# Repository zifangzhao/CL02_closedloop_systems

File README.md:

# CL02 Closed-Loop System

CL02 is a closed-loop electrophysiology trigger controller for detecting configured LFP oscillation features and driving timed stimulation outputs.

The project website is now built from the MkDocs source in [`docs/`](docs/) with configuration in [`mkdocs.yml`](mkdocs.yml). It documents:

- hardware connections and state indicators,
- Windows control-center setup and operation,
- trigger timing and external override behavior,
- firmware update workflow,
- firmware and MATLAB filter-design source locations.

## Local Documentation Preview

```powershell
pip install -r requirements.txt
mkdocs serve
```

For a strict build:

```powershell
mkdocs build --strict --verbose
```

## Repository Areas

| Area | Contents |
| --- | --- |
| `Windows` | CL02 control-center source, installers, and USB driver files. |
| `MCU` | STM32 firmware source, headers, filters, Keil project files, and firmware images. |
| `PCB` | CL02 board files, CAM outputs, assembly files, and BOM assets. |
| `Matlab` | Filter-design and validation scripts. |
| `docs` | MkDocs website source. |

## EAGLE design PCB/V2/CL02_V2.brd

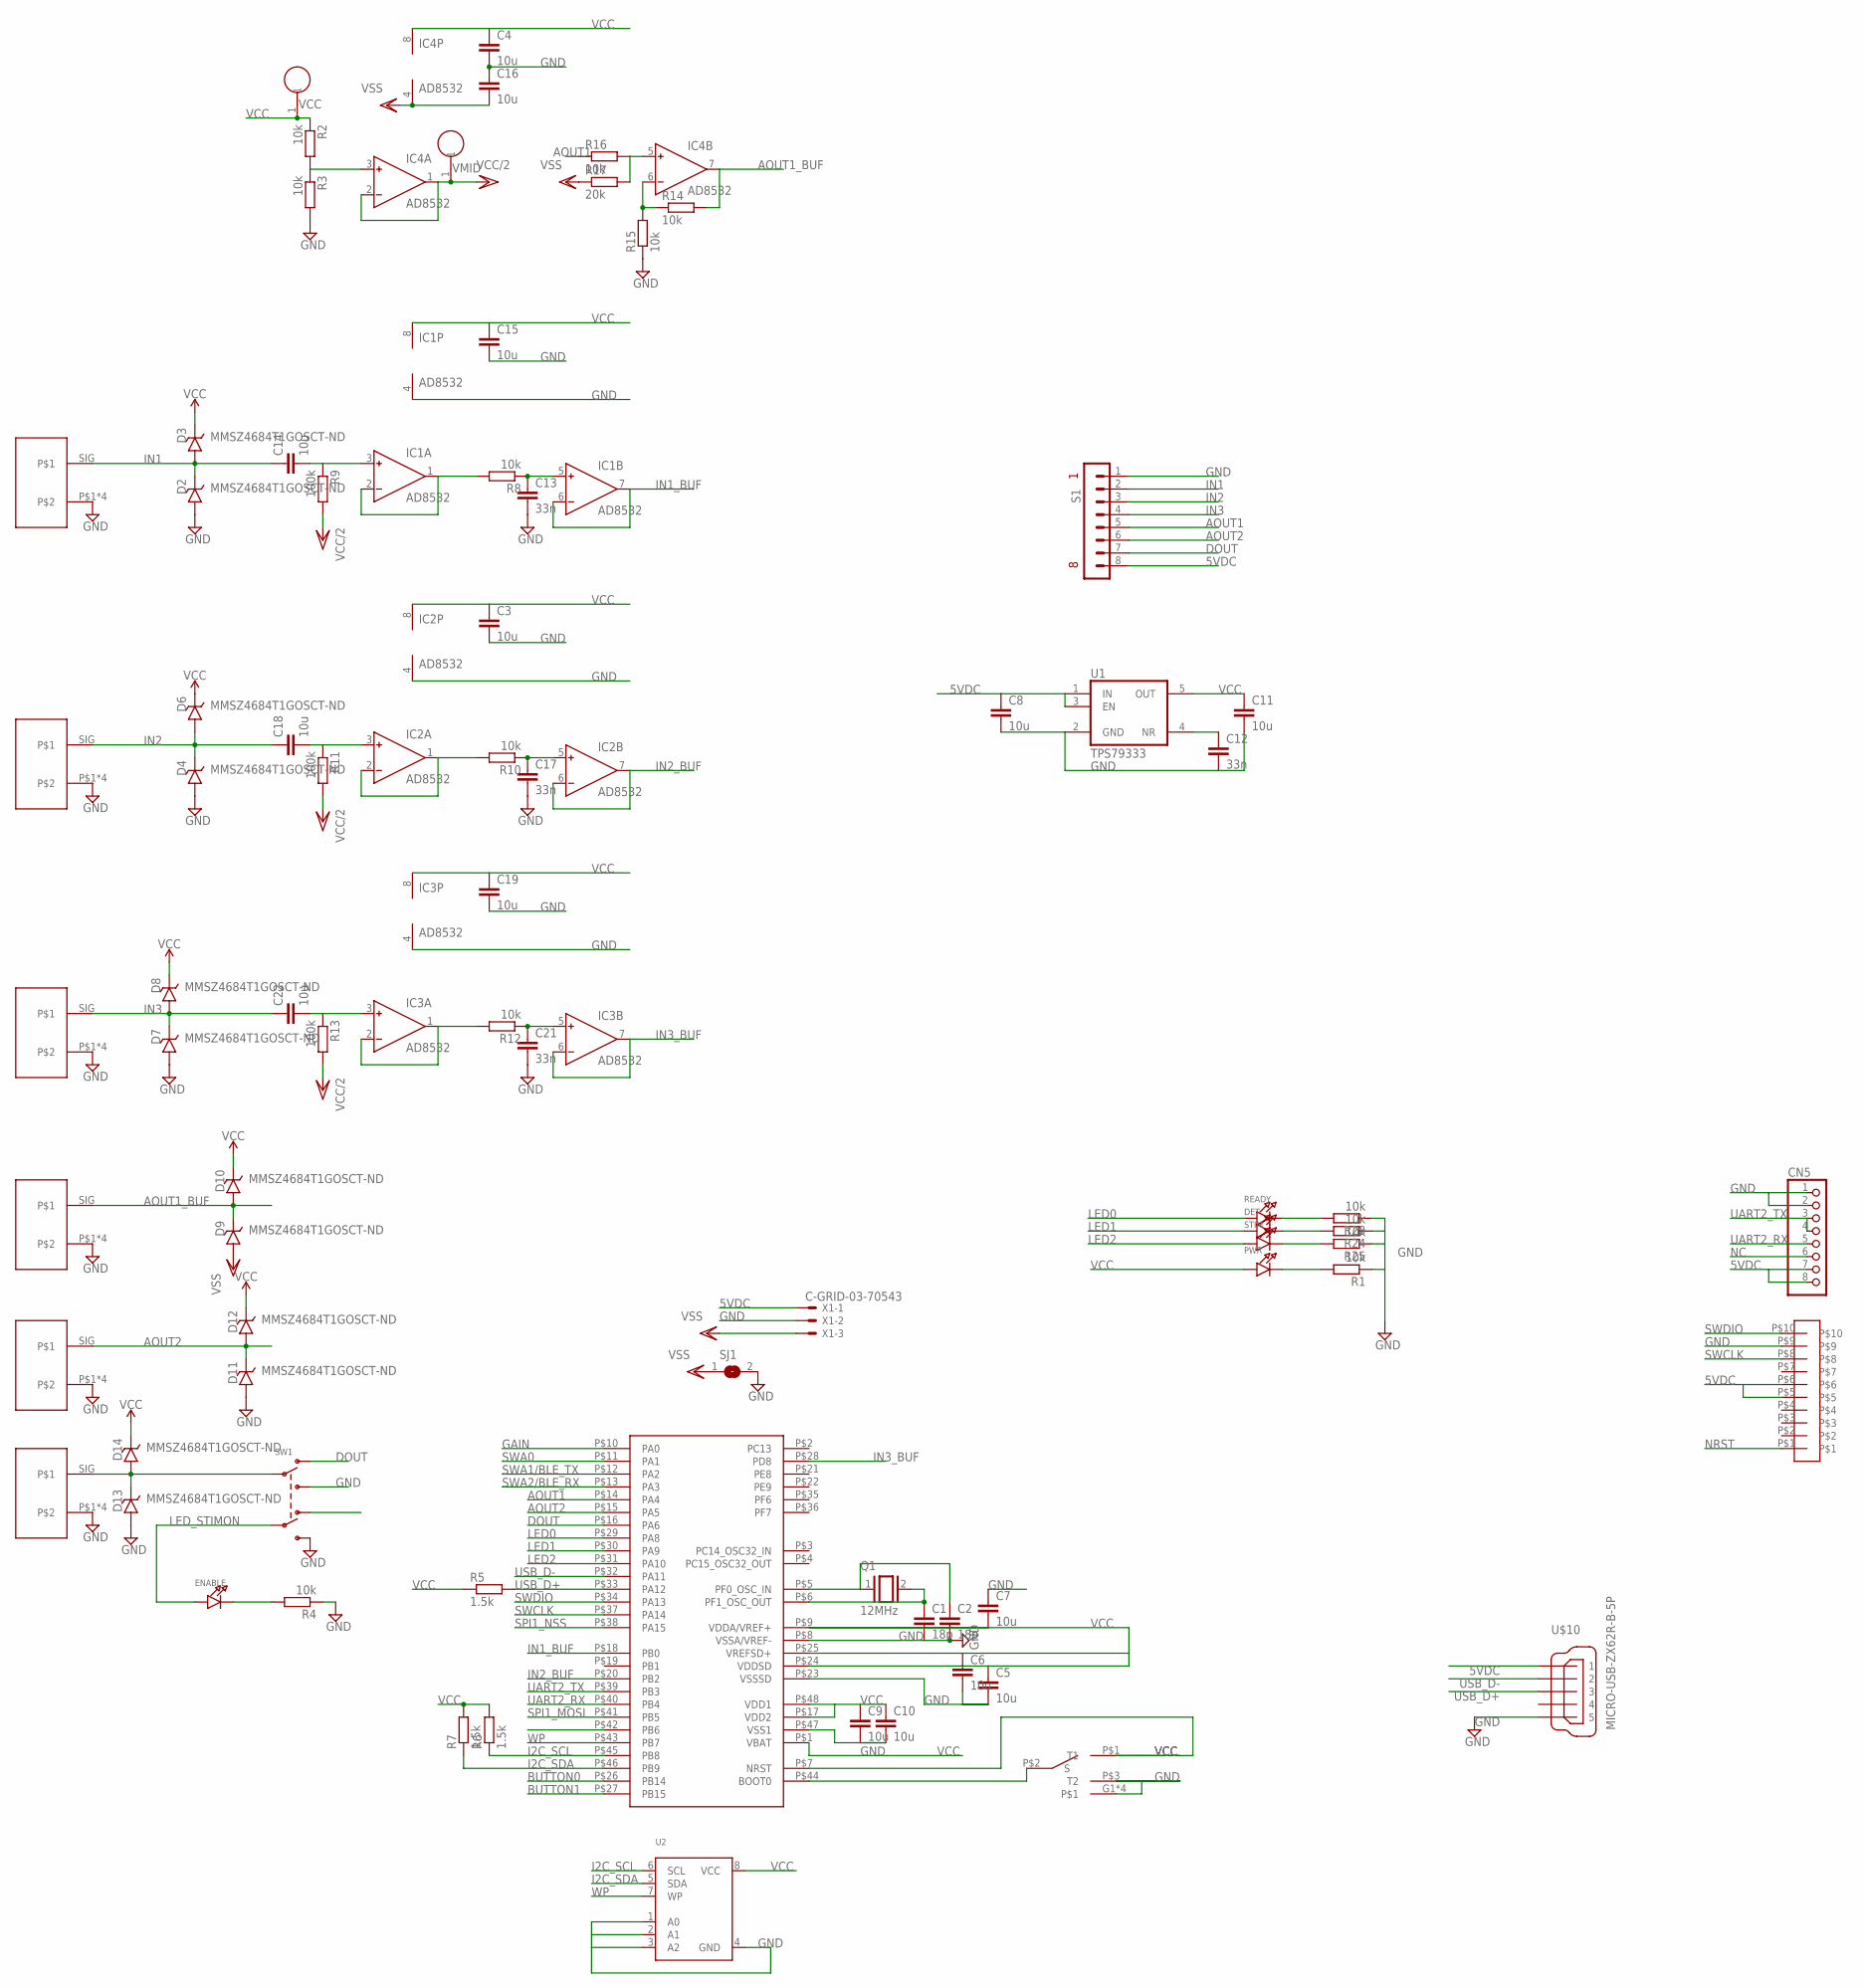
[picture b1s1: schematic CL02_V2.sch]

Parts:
A_OUT1, A_OUT2: BNC_8MM; BNC_V_8MM
C1, C2: 18p; C0402
C3, C4, C5, C6, C7, C8, C9, C10, C11, C14, C15, C16, C18, C19, C22: 10u; C0402
C12, C13, C17, C21: 33n; C0402
CN5: JST_8PIN; JSTPH8
D2, D3, D4, D6, D7, D8, D9, D10, D11, D12, D13, D14: MMSZ4684T1GOSCT-ND; SOD-123
DET: LED0603; CHIPLED_0603
D_OUT: BNC_8MM; BNC_V_8MM
ENABLE: LED0603; CHIPLED_0603
IC1, IC2, IC3, IC4: AD8532; SO8
IN1, IN2, IN3: BNC_8MM; BNC_V_8MM
PWR: LED0603; CHIPLED_0603
Q1: 12MHz; QS
R1, R2, R3, R4, R8, R10, R12, R14, R15, R16, R23, R24, R25: 10k; R0402
R5, R6, R7: 1.5k; R0402
R9, R11, R13: 100k; R0402
R17: 20k; R0402
READY: LED0603; CHIPLED_0603
S1: TERMINAL_BLOCK_8-3.5MM; TERMINAL_BLOCK_3.5MM_8
SJ1: SOLDERJUMPER; SOLDERJUMPER_ARROW_NOPASTE
STIM: LED0603; CHIPLED_0603
SW1: SWITCH_DPDT; DPDT_SMT_JS202011SCQN
U1: TPS79333; TSOT-23-5
U2: EEPROM_I2C_SOIC8_GENERIC; SOIC8_150MIL
U$1: STM32F373CCT6; LQFP48
U$9: 2.54MM_2X5
U$10: MICRO-USB-ZX62R-B-5P; ZX62R-B-5P
U$12: CUS-12B
VCC: TESTPOINT
VMID: TESTPOINT
X1: C-GRID-03-70543; 70543-03

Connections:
5VDC: C8.1, CN5.7, CN5.8, S1.8, U1.1 (IN), U1.3 (EN), U$9.P$5, U$9.P$6, U$10.1, X1.1
AOUT1: R16.1, S1.5, U$1.P$14 (PA4)
AOUT1_BUF: A_OUT1.SIG, D9.1 (C), D10.2 (A), IC4.7 (OUT), R14.2
AOUT2: A_OUT2.SIG, D11.1 (C), D12.2 (A), S1.6, U$1.P$15 (PA5)
BOOT0: U$1.P$44 (BOOT0), U$12.P$2 (S)
BUTTON0: U$1.P$26 (PB14)
BUTTON1: U$1.P$27 (PB15)
DOUT: S1.7, SW1.P$1 (O1), U$1.P$16 (PA6)
GAIN: U$1.P$10 (PA0)
GND: A_OUT1.P$1, A_OUT1.P$2, A_OUT1.P$3, A_OUT1.P$4, A_OUT2.P$1, A_OUT2.P$2, A_OUT2.P$3, A_OUT2.P$4, C1.2, C2.2, C3.2, C4.2, C5.2, C6.2, C7.1, C8.2, C9.2, C10.2, C11.2, C12.2, C13.2, C15.2, C16.1, C17.2, C19.2, C21.2, CN5.1, CN5.2, D2.2 (A), D4.2 (A), D7.2 (A), D11.2 (A), D13.2 (A), D_OUT.P$1, D_OUT.P$2, D_OUT.P$3, D_OUT.P$4, IC1.4 (V-), IC2.4 (V-), IC3.4 (V-), IN1.P$1, IN1.P$2, IN1.P$3, IN1.P$4, IN2.P$1, IN2.P$2, IN2.P$3, IN2.P$4, IN3.P$1, IN3.P$2, IN3.P$3, IN3.P$4, R1.1, R3.2, R4.1, R15.1, R23.1, R24.1, R25.1, S1.1, SJ1.2, SW1.P$3 (S1), SW1.P$4 (S2), U1.2 (GND), U2.1 (A0), U2.2 (A1), U2.3 (A2), U2.4 (GND), U$1.P$8 (VSSA/VREF-), U$1.P$23 (VSSSD), U$1.P$47 (VSS1), U$9.P$9, U$10.5, U$12.G1, U$12.G2, U$12.G3, U$12.G4, U$12.P$3 (T2), X1.2
GPIO3: D13.1 (C), D14.2 (A), D_OUT.SIG, SW1.P$2 (P1)
I2C_SCL: R6.1, U2.6 (SCL), U$1.P$45 (PB8)
I2C_SDA: R7.1, U2.5 (SDA), U$1.P$46 (PB9)
IN1: C14.1, D2.1 (C), D3.2 (A), IN1.SIG, S1.2
IN1_BUF: IC1.6 (IN-), IC1.7 (OUT), U$1.P$18 (PB0)
IN2: C18.1, D4.1 (C), D6.2 (A), IN2.SIG, S1.3
IN2_BUF: IC2.6 (IN-), IC2.7 (OUT), U$1.P$20 (PB2)
IN3: C22.1, D7.1 (C), D8.2 (A), IN3.SIG, S1.4
IN3_BUF: IC3.6 (IN-), IC3.7 (OUT), U$1.P$28 (PD8)
LED0: READY.A, U$1.P$29 (PA8)
LED1: DET.A, U$1.P$30 (PA9)
LED2: STIM.A, U$1.P$31 (PA10)
LED_STIMON: ENABLE.A, SW1.P$5 (P2)
unnamed: C12.1, U1.4 (NR)
unnamed: IC2.1 (OUT), IC2.2 (IN-), R10.2
unnamed: R25.2, STIM.C
unnamed: C17.1, IC2.5 (IN+), R10.1
unnamed: IC1.1 (OUT), IC1.2 (IN-), R8.2
unnamed: C13.1, IC1.5 (IN+), R8.1
unnamed: C2.1, Q1.1, U$1.P$5 (PF0_OSC_IN)
unnamed: C1.1, Q1.2, U$1.P$6 (PF1_OSC_OUT)
unnamed: C18.2, IC2.3 (IN+), R11.1
unnamed: IC4.3 (IN+), R2.2, R3.1
unnamed: IC3.1 (OUT), IC3.2 (IN-), R12.2
unnamed: C21.1, IC3.5 (IN+), R12.1
unnamed: C22.2, IC3.3 (IN+), R13.1
unnamed: C14.2, IC1.3 (IN+), R9.1
unnamed: PWR.C, R1.2
unnamed: IC4.6 (IN-), R14.1, R15.2
unnamed: DET.C, R24.2
unnamed: R23.2, READY.C
unnamed: ENABLE.C, R4.2
unnamed: IC4.5 (IN+), R16.2, R17.2
NC: CN5.6
NRST: U$9.P$1
SPI1_MOSI: U$1.P$41 (PB5)
SPI1_NSS: U$1.P$38 (PA15)
SWA0: U$1.P$11 (PA1)
SWA1/BLE_TX: U$1.P$12 (PA2)
SWA2/BLE_RX: U$1.P$13 (PA3)
SWCLK: U$1.P$37 (PA14), U$9.P$8
SWDIO: U$1.P$34 (PA13), U$9.P$10
UART2_RX: CN5.5, U$1.P$40 (PB4)
UART2_TX: CN5.3, CN5.4, U$1.P$39 (PB3)
USB_D+: R5.2, U$1.P$33 (PA12), U$10.3
USB_D-: U$1.P$32 (PA11), U$10.2
VCC: C3.1, C4.1, C5.1, C6.1, C7.2, C9.1, C10.1, C11.1, C15.1, C19.1, D3.1 (C), D6.1 (C), D8.1 (C), D10.1 (C), D12.1 (C), D14.1 (C), IC1.8 (V+), IC2.8 (V+), IC3.8 (V+), IC4.8 (V+), PWR.A, R2.1, R5.1, R6.2, R7.2, SW1.P$6 (O2), U1.5 (OUT), U2.8 (VCC), U$1.P$1 (VBAT), U$1.P$7 (NRST), U$1.P$9 (VDDA/VREF+), U$1.P$17 (VDD2), U$1.P$24 (VDDSD), U$1.P$25 (VREFSD+), U$1.P$48 (VDD1), U$12.P$1 (T1), VCC.1
VCC/2: IC4.1 (OUT), IC4.2 (IN-), R9.2, R11.2, R13.2, VMID.1
VSS: C16.2, D9.2 (A), IC4.4 (V-), R17.1, SJ1.1, X1.3
WP: U2.7 (WP), U$1.P$43 (PB7)

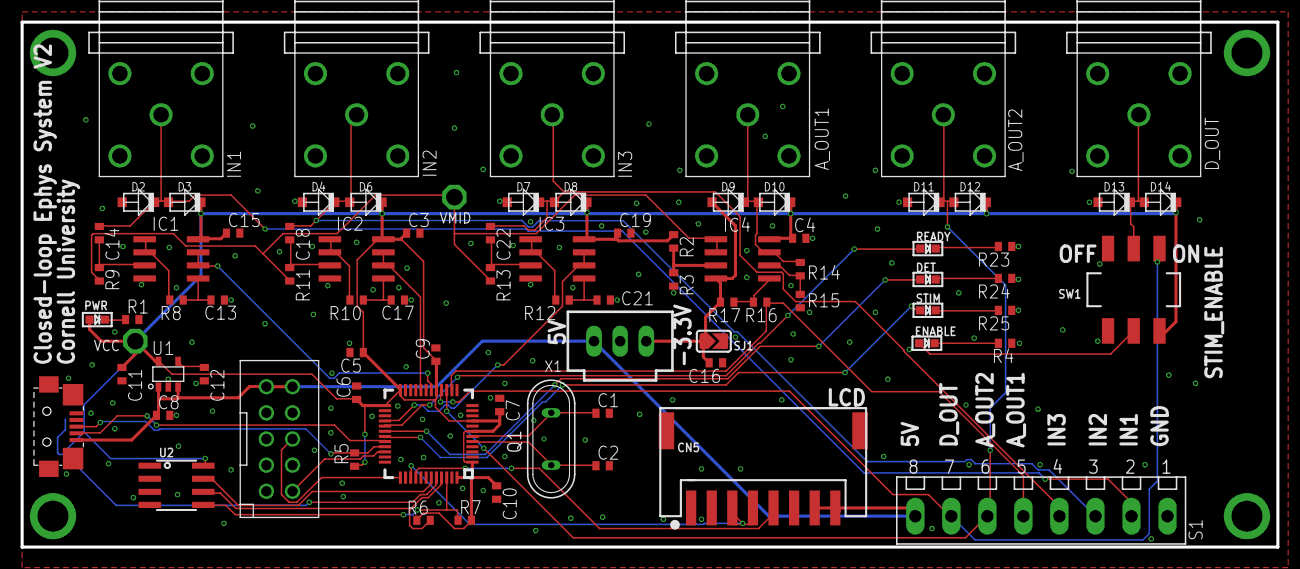
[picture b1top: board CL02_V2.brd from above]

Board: 2 copper layers, 122.0 x 51.0 mm, 82 parts (1 on the bottom side), 50 nets.

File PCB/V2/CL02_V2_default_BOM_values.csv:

Qty,Value,Device,Parts,Package,Description,BOM,MF,MPN,OC_FARNELL,OC_NEWARK,POPULARITY,SPICEMODEL,SPICEPREFIX
1,2.54MM_2X5,2.54MM_2X5,U$9,2.54MM_2X5,,,,,,,,,
4,MCP6007T-E,AD8542R,"IC1, IC2, IC3, IC4",SO8,General-Purpose CMOS Rail-to-Rail Amplifiers,,ALTERA CORPORATION,AD8542ARZ-REEL,1424150,59K6827,0,,
6,BNC_8MM,BNC_8MM,"A_OUT1, A_OUT2, D_OUT, IN1, IN2, IN3",BNC_V_8MM,,,,,,,,,
,,,,,,,,,,,,,
2,18p,CC0402,"C1, C2",C0402,"CAPACITOR, European symbol",,,,,,,NONE,C
15,10u,CC0402,"C3, C4, C5, C6, C7, C8, C9, C10, C11, C14, C15, C16, C18, C19, C22",C0402,"CAPACITOR, European symbol",,,,,,,NONE,C
4,33n,CC0402,"C12, C13, C17, C21",C0402,"CAPACITOR, European symbol",,,,,,,NONE,C
1,CUS-12B,CUS-12B,U$12,CUS-12B,Toggle Switch,,,,,,,,
12,MMSZ4684T1GOSCT-ND,DIODE_ZENER_SOD-123,"D2, D3, D4, D6, D7, D8, D9, D10, D11, D12, D13, D14",SOD-123,Zener diode,,,,,,,,
1,,EEPROM_I2C_SOIC8_GENERIC,U2,SOIC8_150MIL,Note: The same pinout is used for many I2C EEPROMs in SOIC8(150mil) from a variety of manufacturers and in various sizes.,,,,,,,,
1,,JST_8PIN,CN5,JSTPH8,JST 8-Pin Right-Angle Connector,,,,,,,,
5,,LED0603,"DET, ENABLE, PWR, READY, STIM",CHIPLED_0603,LED,,,,,,,,
1,MICRO-USB-ZX62R-B-5P,MICRO-USB-ZX62R-B-5P,U$10,ZX62R-B-5P,Hirose Micro USB Connector,,,,,,,,
3,1.5k,RR0402,"R5, R6, R7",R0402,"RESISTOR, European symbol",,,,,,,NONE,R
3,100k,RR0402,"R9, R11, R13",R0402,"RESISTOR, European symbol",,,,,,,NONE,R
13,10k,RR0402,"R1, R2, R3, R8, R10, R12, R14, R15, R16, R23, R24, R25,R4",R0402,"RESISTOR, European symbol",,,,,,,NONE,R
1,20k,RR0402,R17,R0402,"RESISTOR, European symbol",,,,,,,NONE,R
,,,,,,,,,,,,,
,,,,,,,,,,,,,
1,STM32F373CCT6,STM32F373CCT6,U$1,LQFP48,,,,,,,,,
1,,SWITCH_DPDT,SW1,DPDT_SMT_JS202011SCQN,Switch - DPDT,,,,,,,,
1,TERMINAL_BLOCK_8-3.5MM,TERMINAL_BLOCK_8-3.5MM,S1,TERMINAL_BLOCK_3.5MM_8,8-point terminal block,,,,,,,,
,,,,,,,,,,,,,
1,TPS79333,TPS79333,U1,TSOT-23-5,,,,,,,,,
1,12MHz,XTAL/S,Q1,QS,CRYSTAL,,,,,,,,

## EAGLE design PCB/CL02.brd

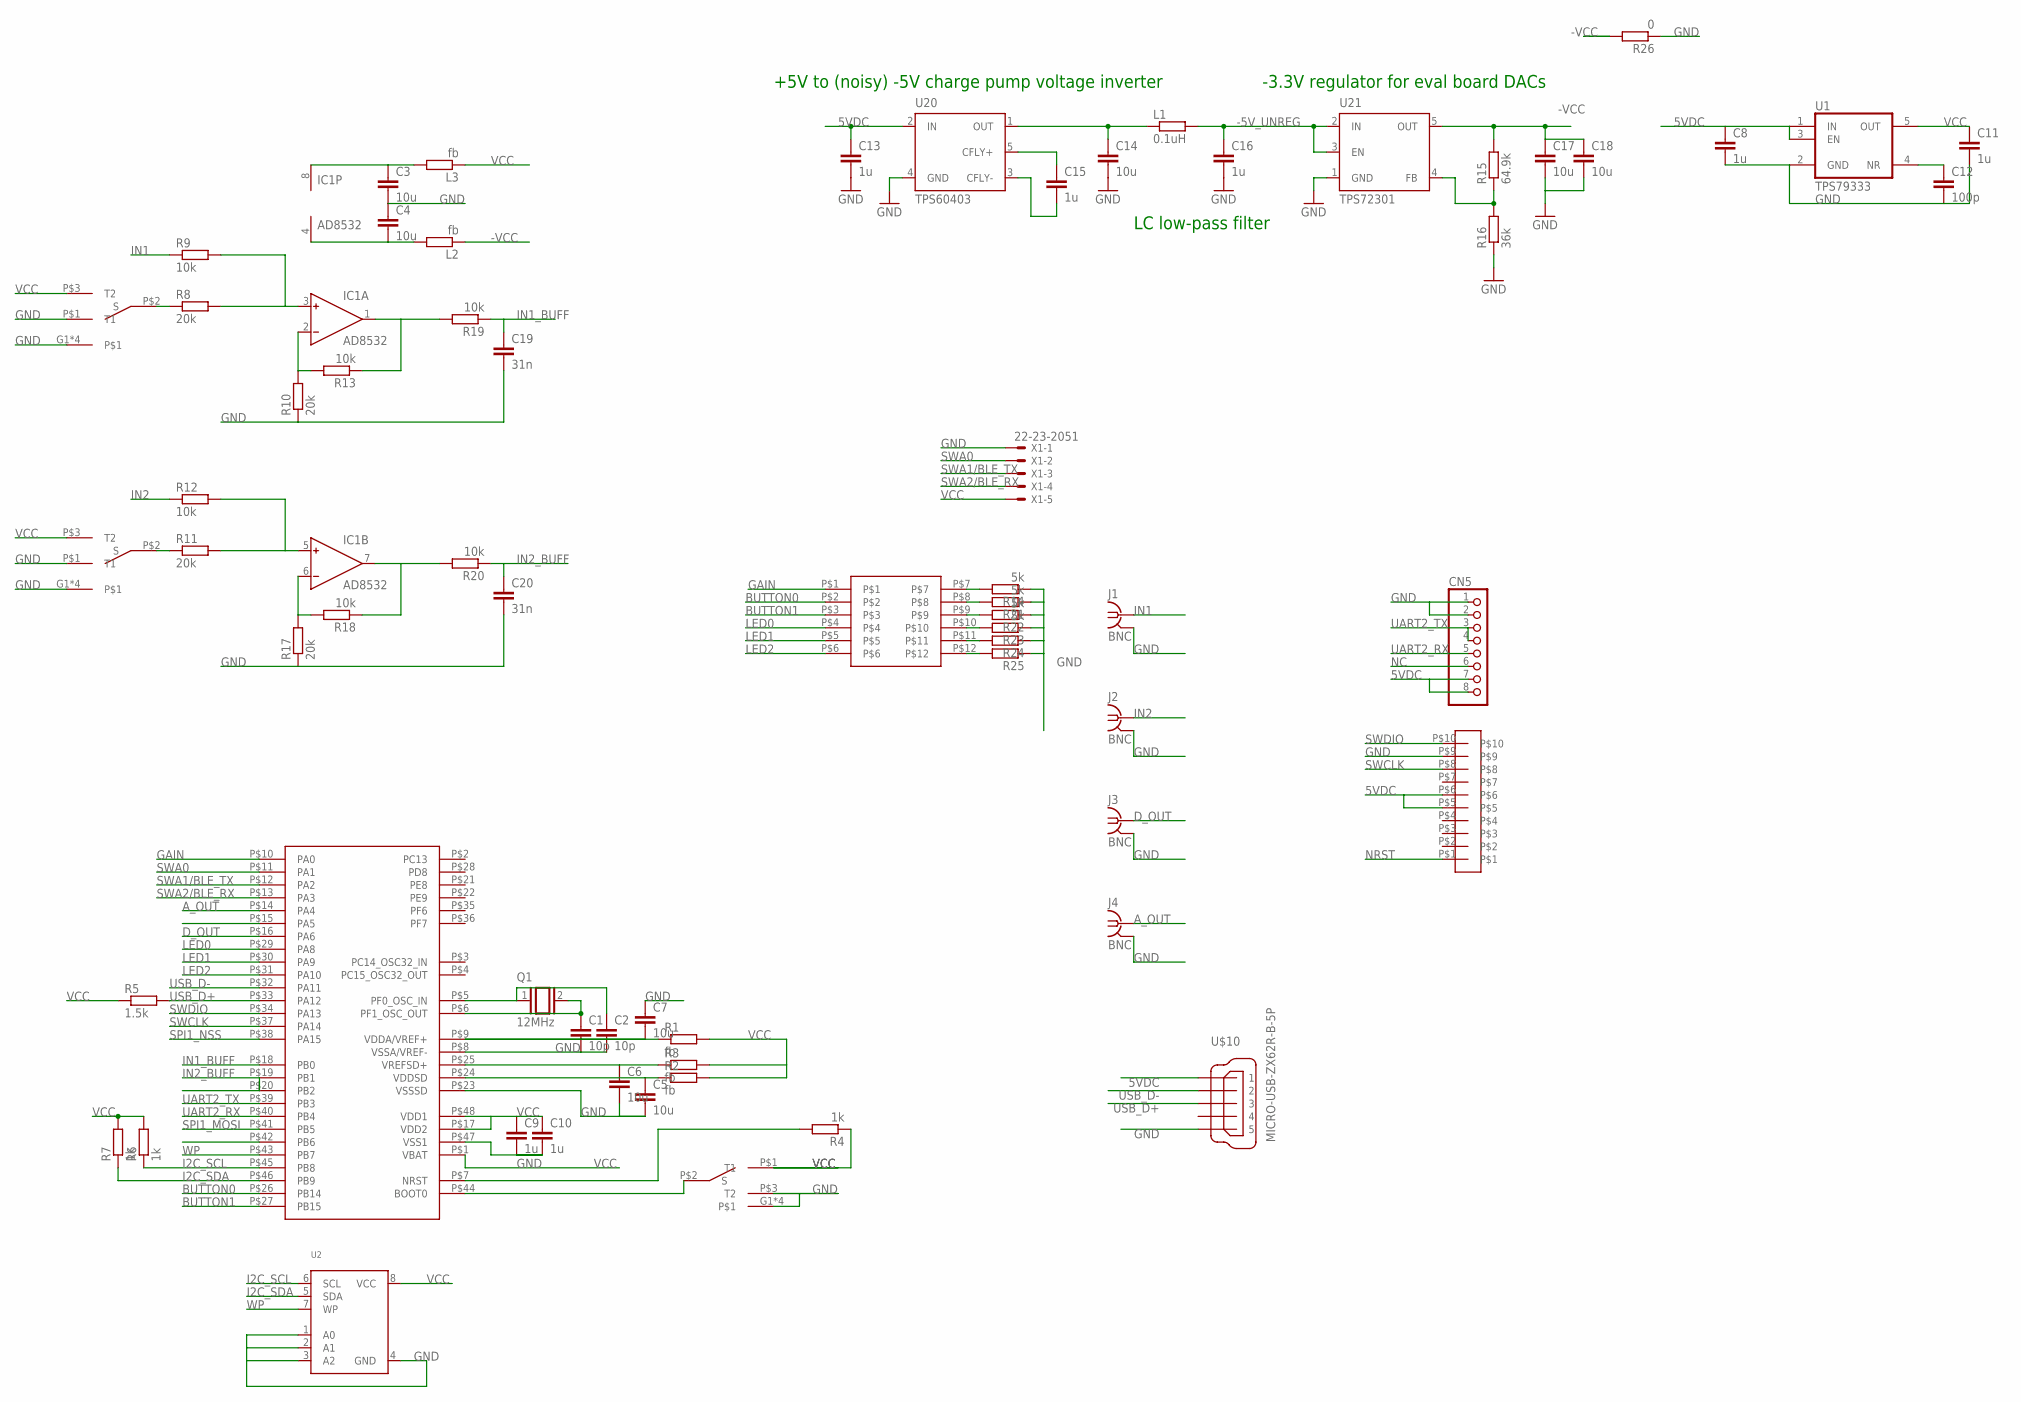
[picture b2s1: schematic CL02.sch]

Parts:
C1, C2: 10p; C0402
C3, C4, C5, C6, C7, C14, C17, C18: 10u; C0402
C8, C9, C10, C11, C13, C15, C16: 1u; C0402
C12: 100p; C0402
C19, C20: 31n; C0402
CN5: JST_8PIN; JSTPH8
IC1: AD8532; SO8
J1, J2, J3, J4: BNC; BNC-SOCKET
L1: 0.1uH; R0402
L2, L3: fb; R0402
Q1: 12MHz; QS
R1, R2, R3: fb; R0402
R4, R6, R7: 1k; R0402
R5: 1.5k; R0402
R8, R10, R11, R17: 20k; R0402
R9, R12, R13, R18, R19, R20: 10k; R0402
R14, R21, R22, R23: 5k; R0402
R15: 64.9k; R0402
R16: 36k; R0402
R24, R25: RR0402; R0402
R26: 0; R0402
U1: TPS79333; TSOT-23-5
U2: EEPROM_I2C_SOIC8_GENERIC; SOIC8_150MIL
U20: TPS60403; SOT-23-5
U21: TPS72301; SOT-23-5
U$1: STM32F373CCT6; LQFP48
U$6, U$7, U$12: CUS-12B
U$8: 2.54MM_2X6
U$9: 2.54MM_2X5
U$10: MICRO-USB-ZX62R-B-5P; ZX62R-B-5P
X1: 22-23-2051

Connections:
5VDC: C8.1, C13.1, CN5.7, CN5.8, U1.1 (IN), U1.3 (EN), U20.2 (IN), U$9.P$5, U$9.P$6, U$10.1
-5V_UNREG: C16.1, L1.2, U21.2 (IN), U21.3 (EN)
-VCC: C17.1, C18.1, L2.1, R15.2, R26.2, U21.5 (OUT)
A_OUT: J4.A (1), U$1.P$14 (PA4)
BOOT0: U$1.P$44 (BOOT0), U$12.P$2 (S)
BUTTON0: U$1.P$26 (PB14), U$8.P$2
BUTTON1: U$1.P$27 (PB15), U$8.P$3
D_OUT: J3.A (1), U$1.P$16 (PA6)
GAIN: U$1.P$10 (PA0), U$8.P$1
GND: C1.2, C2.2, C3.2, C4.1, C5.2, C6.2, C7.1, C8.2, C9.2, C10.2, C11.2, C12.2, C13.2, C14.2, C16.2, C17.2, C18.2, C19.2, C20.2, CN5.1, CN5.2, J1.SH, J2.SH, J3.SH, J4.SH, R10.1, R14.1, R16.1, R17.1, R21.1, R22.1, R23.1, R24.1, R25.1, R26.1, U1.2 (GND), U2.1 (A0), U2.2 (A1), U2.3 (A2), U2.4 (GND), U20.4 (GND), U21.1 (GND), U$1.P$8 (VSSA/VREF-), U$1.P$23 (VSSSD), U$1.P$47 (VSS1), U$6.G1, U$6.G2, U$6.G3, U$6.G4, U$6.P$1 (T1), U$7.G1, U$7.G2, U$7.G3, U$7.G4, U$7.P$1 (T1), U$9.P$9, U$10.5, U$12.G1, U$12.G2, U$12.G3, U$12.G4, U$12.P$3 (T2), X1.1
I2C_SCL: R6.1, U2.6 (SCL), U$1.P$45 (PB8)
I2C_SDA: R7.1, U2.5 (SDA), U$1.P$46 (PB9)
IN1: J1.A (1), R9.1
IN1_BUFF: C19.1, R19.1, U$1.P$18 (PB0)
IN2: J2.A (1), R12.1
IN2_BUFF: C20.1, R20.1, U$1.P$19 (PB1), U$1.P$20 (PB2)
LED0: U$1.P$29 (PA8), U$8.P$4
LED1: U$1.P$30 (PA9), U$8.P$5
LED2: U$1.P$31 (PA10), U$8.P$6
unnamed: C12.1, U1.4 (NR)
unnamed: IC1.2 (IN-), R10.2, R13.2
unnamed: R25.2, U$8.P$12
unnamed: IC1.1 (OUT), R13.1, R19.2
unnamed: C2.1, Q1.1, U$1.P$5 (PF0_OSC_IN)
unnamed: C1.1, Q1.2, U$1.P$6 (PF1_OSC_OUT)
unnamed: IC1.3 (IN+), R8.2, R9.2
unnamed: C5.1, R2.1, U$1.P$24 (VDDSD)
unnamed: C6.1, R3.1, U$1.P$25 (VREFSD+)
unnamed: C7.2, R1.1, U$1.P$9 (VDDA/VREF+)
unnamed: R8.1, U$6.P$2 (S)
unnamed: IC1.6 (IN-), R17.2, R18.2
unnamed: IC1.7 (OUT), R18.1, R20.2
unnamed: IC1.5 (IN+), R11.2, R12.2
unnamed: R11.1, U$7.P$2 (S)
unnamed: C3.1, IC1.8 (V+), L3.2
unnamed: C4.2, IC1.4 (V-), L2.2
unnamed: R24.2, U$8.P$11
unnamed: R23.2, U$8.P$10
unnamed: R22.2, U$8.P$9
unnamed: R21.2, U$8.P$8
unnamed: R14.2, U$8.P$7
unnamed: C15.1, U20.5 (CFLY+)
unnamed: C15.2, U20.3 (CFLY-)
unnamed: R15.1, R16.2, U21.4 (FB)
unnamed: C14.1, L1.1, U20.1 (OUT)
NC: CN5.6
NRST: R4.2, U$1.P$7 (NRST), U$9.P$1
SPI1_MOSI: U$1.P$41 (PB5)
SPI1_NSS: U$1.P$38 (PA15)
SWA0: U$1.P$11 (PA1), X1.2
SWA1/BLE_TX: U$1.P$12 (PA2), X1.3
SWA2/BLE_RX: U$1.P$13 (PA3), X1.4
SWCLK: U$1.P$37 (PA14), U$9.P$8
SWDIO: U$1.P$34 (PA13), U$9.P$10
UART2_RX: CN5.5, U$1.P$40 (PB4)
UART2_TX: CN5.3, CN5.4, U$1.P$39 (PB3)
USB_D+: R5.2, U$1.P$33 (PA12), U$10.3
USB_D-: U$1.P$32 (PA11), U$10.2
VCC: C9.1, C10.1, C11.1, L3.1, R1.2, R2.2, R3.2, R4.1, R5.1, R6.2, R7.2, U1.5 (OUT), U2.8 (VCC), U$1.P$1 (VBAT), U$1.P$17 (VDD2), U$1.P$48 (VDD1), U$6.P$3 (T2), U$7.P$3 (T2), U$12.P$1 (T1), X1.5
WP: U2.7 (WP), U$1.P$43 (PB7)

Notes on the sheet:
-3.3V regulator for eval board DACs
+5V to (noisy) -5V charge pump voltage inverter
LC low-pass filter

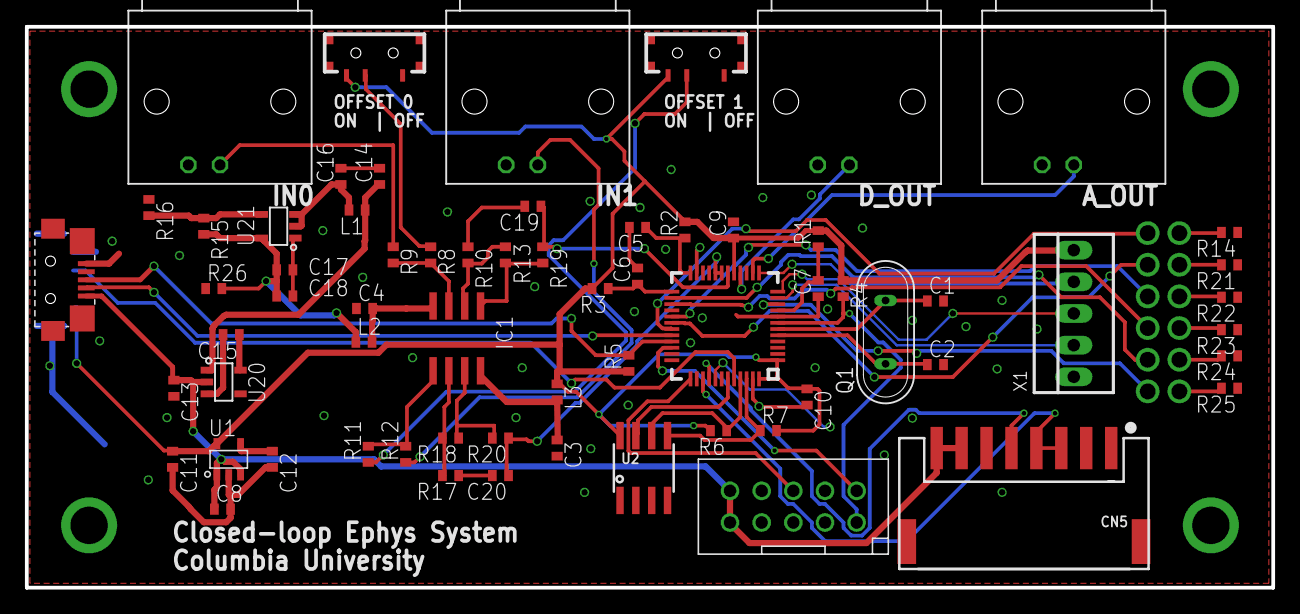
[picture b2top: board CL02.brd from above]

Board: 2 copper layers, 100.0 x 45.0 mm, 68 parts (1 on the bottom side), 57 nets.

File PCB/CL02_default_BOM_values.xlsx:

Qty | Value | Device | Parts | Package | Description | MF | MPN | OC_FARNELL | OC_NEWARK | POPULARITY | SPICEMODEL | SPICEPREFIX
1 | 2.54MM_2X5 | 2.54MM_2X5 | U$9 | 2.54MM_2X5
1 | 2.54MM_2X6 | 2.54MM_2X6 | U$8 | 2.54MM_2X6
1 | 22-23-2051 | 22-23-2051 | X1 | 22-23-2051 | .100 (2.54mm) Center Header - 5 Pin" | MOLEX | 22-23-2051 | 1462952 | 38C9178
1 | AD8532 | AD8542R | IC1 | SO8 | General-Purpose CMOS Rail-to-Rail Amplifiers | ALTERA CORPORATION | AD8542ARZ-REEL | 1424150 | 59K6827 | 0
4 | BNC_8MM | BNC_8MM | U$2, U$3, U$4, U$5 | BNC_V_8MM
1 | 100p | CC0402 | C12 | C0402 | CAPACITOR, European symbol |  |  |  |  |  | NONE | C
2 | 10p | CC0402 | C1, C2 | C0402 | CAPACITOR, European symbol |  |  |  |  |  | NONE | C
8 | 10u | CC0402 | C14, C17, C18,C3, C4, C5, C6, C7 | C0402 | CAPACITOR, European symbol |  |  |  |  |  | NONE | C
6 | 1u | CC0402 | C8, C9, C10, C11, C13, C15, C16 | C0402 | CAPACITOR, European symbol |  |  |  |  |  | NONE | C
2 | 33n | CC0402 | C19, C20 | C0402 | CAPACITOR, European symbol |  |  |  |  |  | NONE | C
3 | CUS-12B | CUS-12B | U$6, U$7, U$12 | CUS-12B | Toggle Switch
1 |  | EEPROM_I2C_SOIC8_GENERIC | U2 | SOIC8_150MIL | Note: The same pinout is used for many I2C EEPROMs in SOIC8(150mil) from a vari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
1 |  | JST_8PIN | CN5 | JSTPH8 | JST 8-Pin Right-Angle Connector
1 | MICRO-USB-ZX62R-B-5P | MICRO-USB-ZX62R-B-5P | U$10 | ZX62R-B-5P | Hirose Micro USB Connector
2 | nc | RR0402 | R24, R25 | R0402 | RESISTOR, European symbol |  |  |  |  |  | NONE | R
1 | 0 | RR0402 | R26 | R0402 | RESISTOR, European symbol |  |  |  |  |  | NONE | R
1 | 0.1uH | RR0402 | L1 | R0402 | RESISTOR, European symbol |  |  |  |  |  | NONE | R
1 | 1.5k | RR0402 | R5 | R0402 | RESISTOR, European symbol |  |  |  |  |  | NONE | R
6 | 10k | RR0402 | R9, R12, R13, R18, R19, R20 | R0402 | RESISTOR, European symbol |  |  |  |  |  | NONE | R
3 | 1k | RR0402 | R4, R6, R7 | R0402 | RESISTOR, European symbol |  |  |  |  |  | NONE | R
4 | 20k | RR0402 | R8, R10, R11, R17 | R0402 | RESISTOR, European symbol |  |  |  |  |  | NONE | R
1 | 36k | RR0402 | R16 | R0402 | RESISTOR, European symbol |  |  |  |  |  | NONE | R
4 | 5k | RR0402 | R14, R21, R22, R23 | R0402 | RESISTOR, European symbol |  |  |  |  |  | NONE | R
1 | 64.9k | RR0402 | R15 | R0402 | RESISTOR, European symbol |  |  |  |  |  | NONE | R
5 | BLM15 | RR0402 | L2, L3, R1, R2, R3 | R0402 | RESISTOR, European symbol |  |  |  |  |  | NONE | R
1 | STM32F373CCT6 | STM32F373CCT6 | U$1 | LQFP48
1 | MAX829EUK+T | TPS60403 | U20 | SOT-23-5 | Texas Instruments TPS60403 voltage inverter
1 | TPS72301 | TPS72301 | U21 | SOT-23-5 | Texas Instruments TPS62301 adjustable negative regulator
1 | NCP511SN33T1G | TPS79333 | U1 | TSOT-23-5
1 | 12MHz | XTAL/S | Q1 | QS | CRYSTAL

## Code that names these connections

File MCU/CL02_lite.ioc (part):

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Mcu.Name=STM32F373C(8-B-C)Tx
Mcu.Package=LQFP48
Mcu.UserName=STM32F373CCTx
PA0.GPIOParameters=GPIO_Label
PA0.GPIO_Label=GAIN
PA0.Mode=IN0
PA0.Signal=ADC1_IN0
PA10.GPIOParameters=GPIO_Label
PA10.GPIO_Label=LED0
PA10.Signal=GPIO_Output
PA11.Mode=Device
PA11.Signal=USB_DM
PA12.Mode=Device
PA12.Signal=USB_DP
PA13.Mode=Serial_Wire
PA13.Signal=SYS_JTMS-SWDIO
PA14.Mode=Serial_Wire
PA14.Signal=SYS_JTCK-SWCLK
PA2.GPIOParameters=GPIO_Speed
PA2.GPIO_Speed=GPIO_SPEED_FREQ_HIGH
PA2.Signal=S_TIM2_CH3
PA4.GPIOParameters=GPIO_Label
PA4.GPIO_Label=AOUT
PA4.Signal=COMP_DAC11_group
PA5.GPIOParameters=GPIO_Label
PA5.GPIO_Label=DOUT1
PA5.Signal=GPIO_Output
PA6.GPIOParameters=GPIO_Label
PA6.GPIO_Label=DOUT
PA6.Signal=GPIO_Output
PA8.GPIOParameters=GPIO_Label
PA8.GPIO_Label=LED2
PA8.Signal=S_TIM5_CH1_ETR
PA9.GPIOParameters=GPIO_Label
PA9.GPIO_Label=LED1
PA9.Signal=GPIO_Output
PB0.GPIOParameters=GPIO_Label
PB0.GPIO_Label=IN0
PB0.Mode=IN6-Single-Ended zero reference
PB0.Signal=SDADC1_AIN6P
PB1.GPIOParameters=GPIO_Label
PB1.GPIO_Label=IN2_back
PB1.Signal=GPIO_Analog
PB14.Signal=GPIO_Input
PB15.GPIOParameters=GPIO_Label
PB15.GPIO_Label=BUTTON0
PB15.Signal=GPIO_Input
PB2.GPIOParameters=GPIO_Label
PB2.GPIO_Label=IN1
PB2.Signal=SharedAnalog_PB2
PB3.GPIOParameters=GPIO_PuPd,GPIO_ModeDefaultEXTI
PB3.GPIO_ModeDefaultEXTI=GPIO_MODE_IT_RISING_FALLING
PB3.GPIO_PuPd=GPIO_PULLDOWN
PB3.Signal=GPXTI3
PB4.Signal=USART2_RX
PB5.Signal=SPI1_MOSI
PB8.GPIOParameters=GPIO_Pu
PB8.GPIO_Pu=GPIO_PULLUP
PB8.Mode=I2C
PB8.Signal=I2C1_SCL
PB9.GPIOParameters=GPIO_Pu
PB9.GPIO_Pu=GPIO_PULLUP
PB9.Mode=I2C
PB9.Signal=I2C1_SDA
PD8.GPIOParameters=GPIO_Label
PD8.GPIO_Label=IN3
PD8.Mode=IN6-Single-Ended zero reference
PD8.Signal=SDADC3_AIN6P
PF0-OSC_IN.Mode=HSE-External-Oscillator
PF0-OSC_IN.Signal=RCC_OSC_IN
PF1-OSC_OUT.Mode=HSE-External-Oscillator
PF1-OSC_OUT.Signal=RCC_OSC_OUT
RCC.HSEPLLFreq_Value=12000000
RCC.HSE_VALUE=12000000
RCC.SYSCLKFreq_VALUE=72000000
RCC.SYSCLKSource=RCC_SYSCLKSOURCE_PLLCLK
board=CL04_Lite

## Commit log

2021-11-05 Initial commit, V1.04
2021-12-23 V1.0.0.5 Add support of random trigger
2021-12-23 Generated DFU file
2021-12-23 Removed excess files
2021-12-24 Update a new MarkDown document
2022-01-04 % major update V1.0.1.0 Improved wave display, solved sub-sampling problem Change random trigger timer base to 100ms. Added a firmVersion to systemParam Added a copy byte limitation guard to cmd_svr 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
2022-02-04 Bug fix, found a display bug will cause program crash around 40mins
2022-02-04 V1.0.1.1 publish
2022-06-10 Major upgrade 1_0_2_0 Add support of cascade/Gated mode
2023-09-19 minor update
2024-01-04 Fixed gated mode with two threshold controls. Known bug: If triggered too fast, the stimulator will stuck and will not come back unless a hard reset
2024-01-10 V1.0.6 added 100-200,8-40Hz filter
2024-01-11 V1.0.7: fixed DSP id setting mixing problem Added 2nd custom filter support
2024-01-12 Added CL02_FilterDesigner.m
2024-02-05 Rectifier Lowpass filter changed to butterworth
2024-02-05 Ported Pin def to V2.0 board
2024-02-29 % version 2_0_2_0 Trigger signal output at AOUT2 Stim off will not turn filter off Filter updated with order1 IIR Filter generation file in Matlab
2024-03-01 Fixed delay function in C# Added trigger on-hold function (Trigger on First/Last event)
2024-03-08 Uploaded V2 PCB
2024-04-02 Updated filter
2024-08-19 thinkpad L13
2024-08-19 Improved Delta filter
2024-10-24 HTF filter generation
2024-10-25 Testing new hilbert transformer
2024-11-18 Script for configure Moku:G0 for CL02 interfacing to opto
2024-12-19 Improved bluetooth realibility Added periodic Ztest mode Added fast boot mode (for Ztest(
2025-01-15 V2.2.0.0 phase selectiion available
2025-01-16 phase trigger logic improve
2025-01-16 Filter update: THeta changed to 4-12 Hz
2025-01-16 Update theta filter to optimize phase
2025-01-17 in progress to improve phase decoding, with different filters
2025-01-17 Filter update Reordered filterdef.h
2025-01-17 git ignore: added .s
2025-01-17 updated filters with individual variable names. added command 15 support in device for uploading CL paramters
2025-01-17 fixed bug, cmd15 working
2025-01-17 V2.2.0.1 windows app
2025-05-28 Bug correction: 2.2.1.0 1. disabled DAC gain, and fixed it to 1.0 to avoid display scaling problem 2. corrected a bug that set DAC mode wrong everytime after loading
2025-12-05 Updated PCB production files with latest partlist
2025-12-05 Removed outdated bom files
2026-01-03 Uploaded filter simulation/generation files in matlab
2026-01-03 Updated dataMGR to avoid racing conditions induced processing delay
2026-03-10 Update CMSIS DSP and NN libraries, refine STM32F3xx HAL/LL drivers, and adjust USB device configuration while removing unused components.
2026-03-10 Generate code using cubemx on linux
2026-03-11 Add linux specific build files
2026-03-11 Update PB3 pin trigger interrupt callback using cubeMX gen code & simplify TTL handling
2026-03-11 Set up MCU project configuration for linux
2026-03-12 feat: Implement cross-platform GUI and data handling for CL02 closed-loop system
    - Added `data_source.py` for a NumPy-backed circular buffer to store multi-channel data efficiently.
    - Developed `main_window.py` using PyQt6 and pyqtgraph to create a GUI that replicates the functionality of the original C# WinForms application.
    - Introduced `serial_comm.py` to manage serial communication with the CL02 MCU, including port discovery and command handling.
    - Created `main.py` as the entry point for the application, setting up logging and launching the main window.
    - Added `requirements.txt` to specify dependencies for the project, including PyQt6, pyqtgraph, pyserial, and NumPy.
2026-03-12 Refactor CL02 Closed-Loop System GUI to use qtpy and magic-class
    - Updated imports to use qtpy instead of PyQt6 for better compatibility.
    - Introduced magic-class for panel management, creating TriggerDSPPanel, ConnectionPanel, and DisplayPanel.
    - Refactored MainWindow to initialize panels and bind them to the host.
    - Removed legacy panel building methods and replaced them with magic-class implementations.
    - Updated requirements.txt to include magic-class and qtpy dependencies.
2026-03-13 style: Lint w/ ruff
2026-03-13 feat: Add parameter save/load functionality to the CL02 closed-loop system GUI
2026-03-13 feat: Enhance Trigger/DSP panel layout with group boxes and splitter for improved UI organization
2026-03-31 Updated BNC connector info
2026-06-17 Add CL02 MkDocs website
2026-06-28 Disabled automatic comport search

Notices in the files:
parts and their libraries:
microbuilder: This work is placed in the public domain, and may be freely used for commercial and non-commercial work with the following conditions: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
SparkFun-PowerSymbols: Licensing: Creative Commons ShareAlike 4.0 International - https://creativecommons.org/licenses/by-sa/4.0
